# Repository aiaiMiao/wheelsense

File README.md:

# WheelSense

### Hardware

- 5 [infrared distance sensor](https://www.sparkfun.com/products/242)
- 1 [piezo Buzzer](https://www.adafruit.com/product/160)
- 2 [ultrasonic range finder](https://www.parallax.com/product/28015)
- 2 [coin vibrational motors](http://www.robotshop.com/en/2mm-mini-vibrating-disk-motor.html)
- 1 [Arduino Uno](https://store.arduino.cc/arduino-genuino/arduino-uno-rev3)
- 7 x 3-pin and 2 x 2-pin [screw-terminal headers](https://www.pololu.com/category/177/0.1-2.54-mm-screw-terminal-blocks)
- [Ribbon cable wires](https://www.amazon.com/Ribbon-Cable-10-wire-15ft/dp/B007R9SQQM)

### Tools
- Soldering Iron, Solder
- Wire Strippers
- Zip Ties (for wire management)
- Double-Sided Adhesive Tape
- Electrical Tape
- 3D Printer, Filament, Driver Software

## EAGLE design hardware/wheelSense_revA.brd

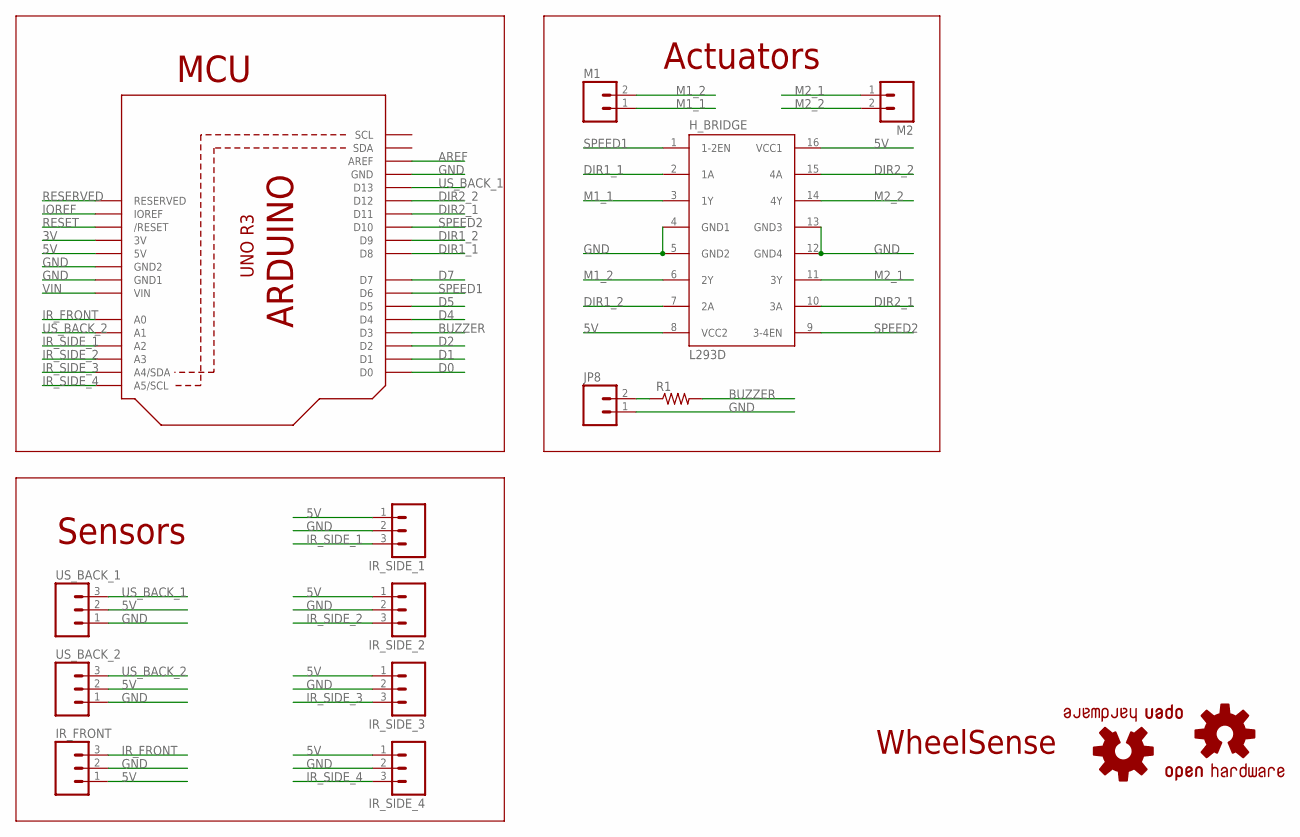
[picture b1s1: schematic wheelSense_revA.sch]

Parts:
H_BRIDGE: L293D; DIL16
IR_FRONT: M03POLAR; MOLEX-1X3
IR_SIDE_1, IR_SIDE_2, IR_SIDE_3, IR_SIDE_4: M03POLAR; MOLEX-1X3
JP8: M02POLAR; MOLEX-1X2
LOGO1, LOGO2: OSHW-LOGOL-TOP; OSHW_LOGO_L_TOP
M1, M2: M02POLAR; MOLEX-1X2
R1: RESISTORPTH-1/4W; AXIAL-0.4
U$1: ARDUIN0R3_NOHOLES; ARDUINOR3-NOHOLES
US_BACK_1, US_BACK_2: M03POLAR; MOLEX-1X3

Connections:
3V: U$1.3V
5V: H_BRIDGE.8 (VCC2), H_BRIDGE.16 (VCC1), IR_FRONT.1, IR_SIDE_1.1, IR_SIDE_2.1, IR_SIDE_3.1, IR_SIDE_4.1, U$1.5V, US_BACK_1.2, US_BACK_2.2
AREF: U$1.AREF
BUZZER: R1.P$2 (2), U$1.D3
D0: U$1.D0
D1: U$1.D1
D2: U$1.D2
D4: U$1.D4
D5: U$1.D5
D7: U$1.D7
DIR1_1: H_BRIDGE.2 (1A), U$1.D8
DIR1_2: H_BRIDGE.7 (2A), U$1.D9
DIR2_1: H_BRIDGE.10 (3A), U$1.D11
DIR2_2: H_BRIDGE.15 (4A), U$1.D12
GND: H_BRIDGE.4 (GND1), H_BRIDGE.5 (GND2), H_BRIDGE.12 (GND4), H_BRIDGE.13 (GND3), IR_FRONT.2, IR_SIDE_1.2, IR_SIDE_2.2, IR_SIDE_3.2, IR_SIDE_4.2, JP8.1, U$1.GND, U$1.GND1, U$1.GND2, US_BACK_1.1, US_BACK_2.1
IOREF: U$1.IOREF
IR_FRONT: IR_FRONT.3, U$1.A0
IR_SIDE_1: IR_SIDE_1.3, U$1.A2
IR_SIDE_2: IR_SIDE_2.3, U$1.A3
IR_SIDE_3: IR_SIDE_3.3, U$1.A4 (A4/SDA)
IR_SIDE_4: IR_SIDE_4.3, U$1.A5 (A5/SCL)
M1_1: H_BRIDGE.3 (1Y), M1.1
M1_2: H_BRIDGE.6 (2Y), M1.2
M2_1: H_BRIDGE.11 (3Y), M2.1
M2_2: H_BRIDGE.14 (4Y), M2.2
unnamed: JP8.2, R1.P$1 (1)
RESERVED: U$1.RESERVED
RESET: U$1.RESET (/RESET)
SPEED1: H_BRIDGE.1 (1-2EN), U$1.D6
SPEED2: H_BRIDGE.9 (3-4EN), U$1.D10
US_BACK_1: U$1.D13, US_BACK_1.3
US_BACK_2: U$1.A1, US_BACK_2.3
VIN: U$1.VIN

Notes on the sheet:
MCU
Sensors
Actuators
WheelSense

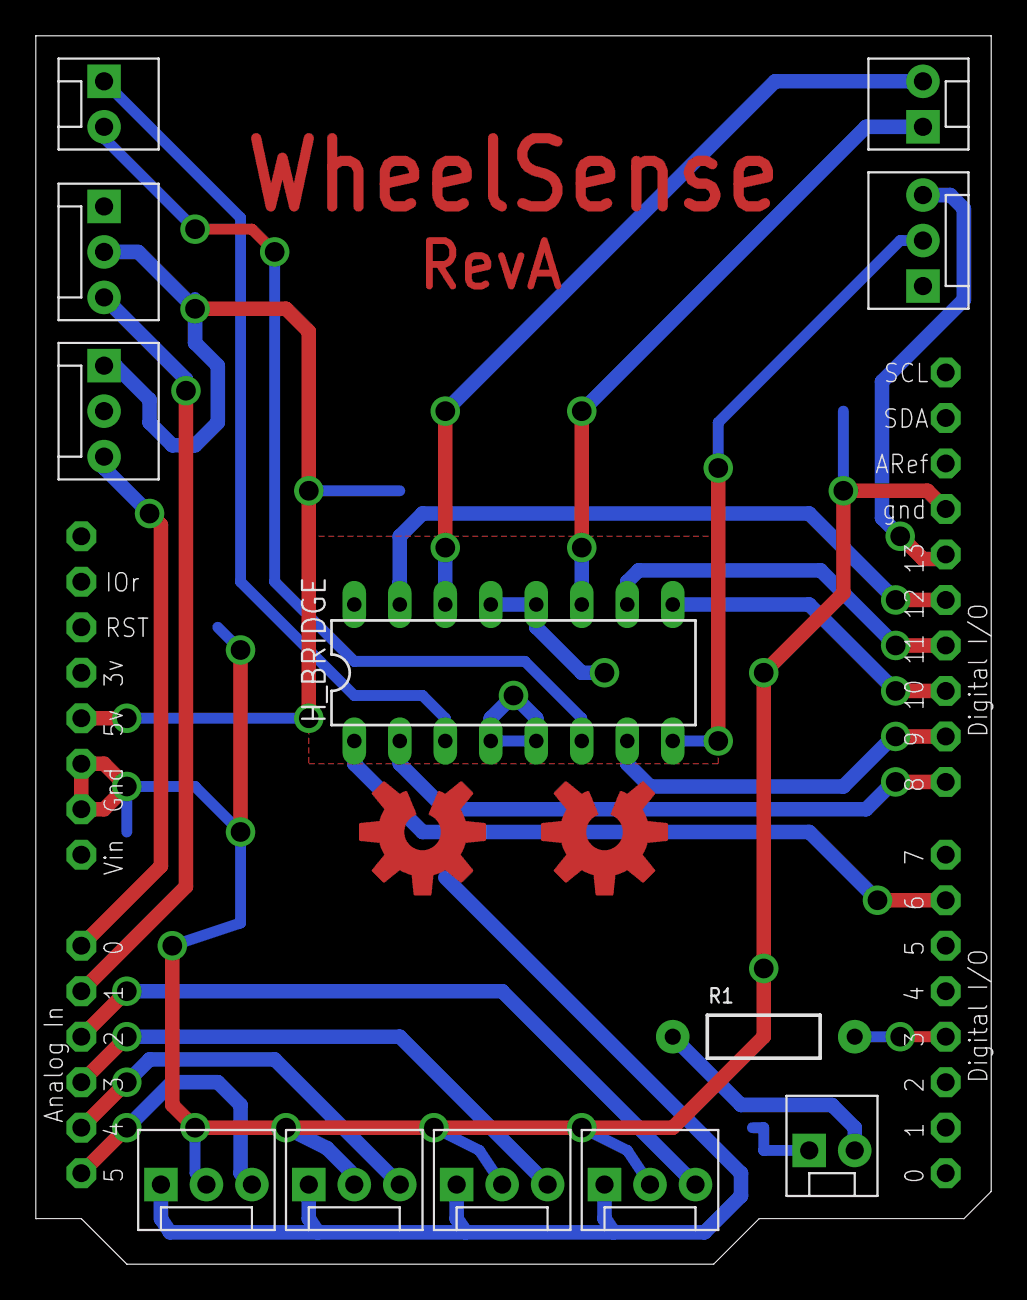
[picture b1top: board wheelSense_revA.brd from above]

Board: 2 copper layers, 53.3 x 68.6 mm, 15 parts (0 on the bottom side), 21 nets.

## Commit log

2016-08-18 Update LICENSE
    add everyone
2016-08-18 Update LICENSE
2016-08-18 add sensors code
2016-08-19 update code
2016-08-19 buzzer and long-range ultrasonic range finder
2016-08-19 working haptics!
2016-08-20 updated backward code
2016-08-20 libs
2016-08-20 add tests
2016-08-20 update scripts
2016-08-20 update buzzer pot for arduino
2016-08-21 handle front and back in buzzer
2016-08-21 better delays for ramp detection
2016-08-21 better delay
2016-08-21 steph test
2016-08-21 remove DS_store
2016-08-21 all sensors included(4)
2016-08-21 merge2
2016-08-21 change pins
2016-08-21 update thresholds and sensor pins
2016-08-21 plotting
2016-08-21 small fixes
2016-08-21 update ramp sensors
2016-08-21 small fixes from testing
2017-04-12 latest code
2017-04-20 cleaning repo
2017-04-20 readme and more cleaning
2017-04-20 added 3d model files, both STL and gcode

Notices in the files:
parts and their libraries:
SparkFun-Connectors: Licensing: Creative Commons ShareAlike 4.0 International - https://creativecommons.org/licenses/by-sa/4.0
microbuilder: This work is placed in the public domain, and may be freely used for commercial and non-commercial work with the following conditions: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
